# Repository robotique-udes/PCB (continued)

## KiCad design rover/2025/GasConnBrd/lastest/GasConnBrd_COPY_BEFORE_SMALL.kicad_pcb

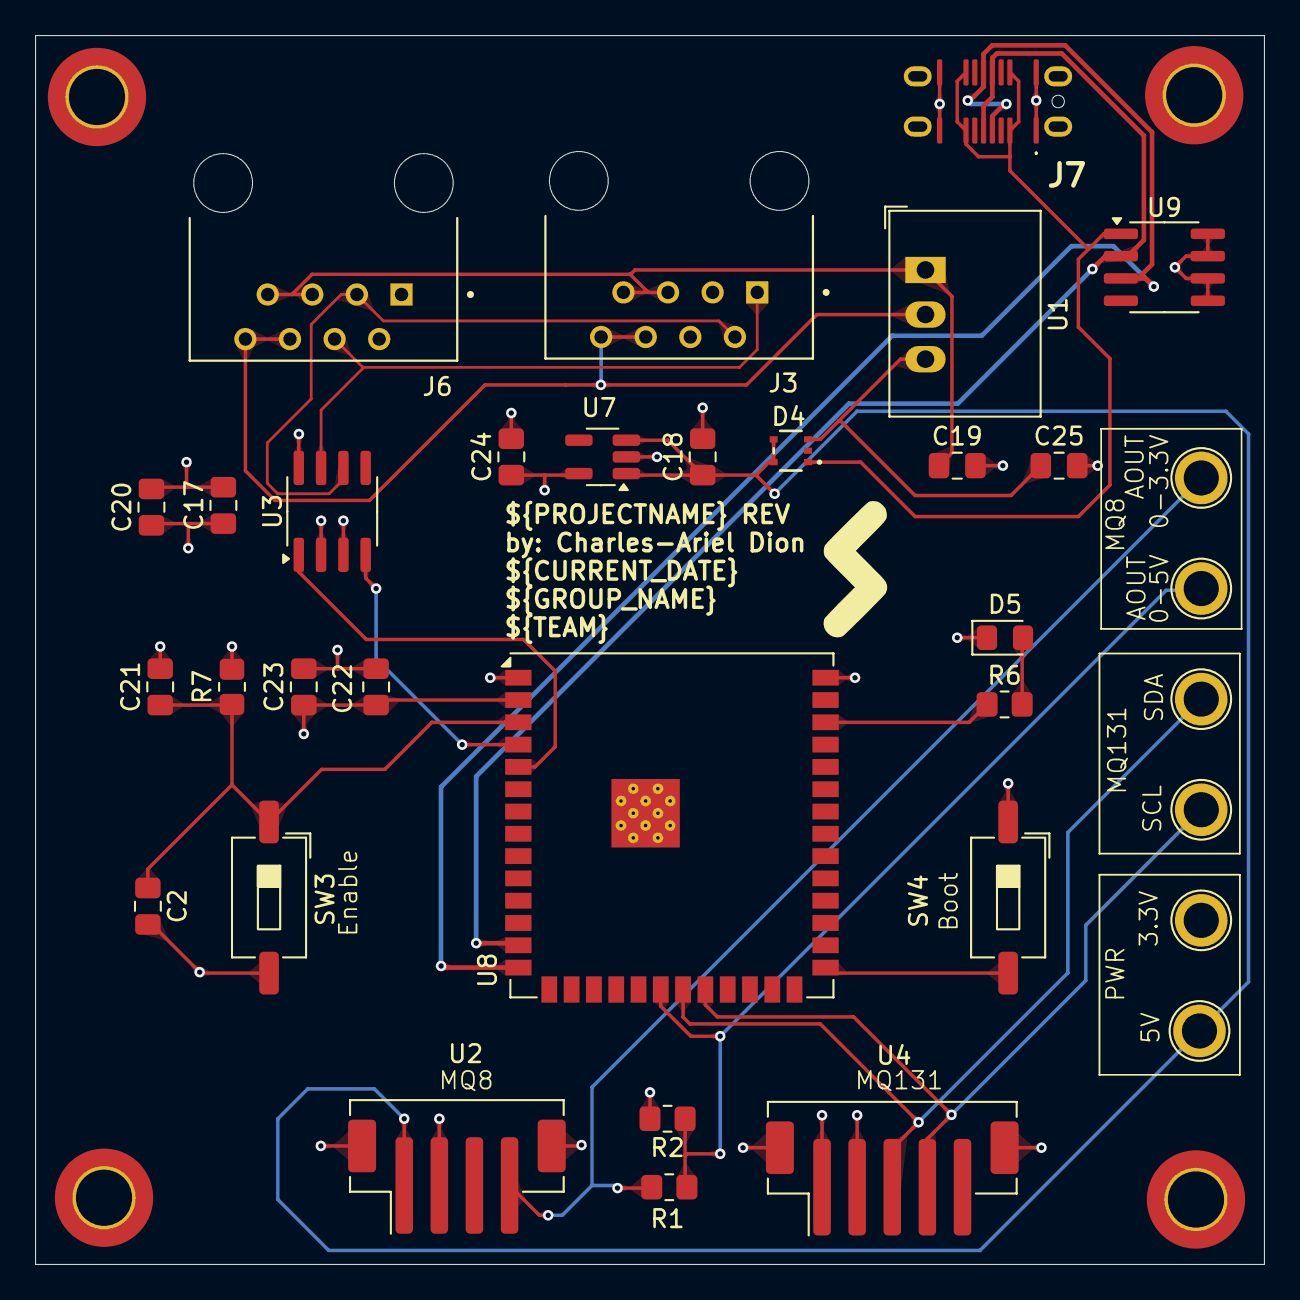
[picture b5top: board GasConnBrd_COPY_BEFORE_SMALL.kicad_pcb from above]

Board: 4 copper layers, 70.0 x 70.0 mm, 38 parts (0 on the bottom side), 20 nets.

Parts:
C2, C20, C23: 100nF; C_0805_2012Metric_Pad1.18x1.45mm_HandSolder
C17, C18, C19, C22, C24, C25: 10uF; C_0805_2012Metric_Pad1.18x1.45mm_HandSolder
C21: 1uF; C_0805_2012Metric_Pad1.18x1.45mm_HandSolder
D4: CVJ10F30; Diode_schottky-CVJ10F30
D5: B; LED_0805_2012Metric_Pad1.15x1.40mm_HandSolder
H9, H10, H11, H12: MountingHole_Pad; MountingHole
J3, J6: Eth-Horiz; Ethernet_Horizontal
J7: USB_C_USB4145-GCT; USB4145_GCT
R1, R7: 10k; R_0805_2012Metric_Pad1.20x1.40mm_HandSolder
R2: 20k; R_0805_2012Metric_Pad1.20x1.40mm_HandSolder
R6: 1k; R_0805_2012Metric_Pad1.20x1.40mm_HandSolder
SW3, SW4: TS09-63-25-WT-160-SMT-TR; SW_DIP_SPSTx01_Slide_6.7x4.1mm_W8.61mm_P2.54mm_LowProfile
TP1, TP2, TP3, TP4, TP6, TP7: TestPoint; TestPoint_Plated_Hole_D2.0mm
U1: R-78E5.0-0.5; Converter_DCDC_RECOM_R-78E-0.5_THT
U2: MQ-8; JST_PH_B4B-PH-SM4-TB_1x04-1MP_P2.00mm_Vertical
U3: SN65HVD232; SOIC-8_3.9x4.9mm_P1.27mm
U4: MQ-131; JST_PH_B5B-PH-SM4-TB_1x05-1MP_P2.00mm_Vertical
U7: LDO-TLV74033PDBVR; SOT-23-5_HandSoldering
U8: ESP32-S3-WROVER; ESP32-S3-WROOM-1U
U9: TVS; SOIC-8_3.9x4.9mm_P1.27mm

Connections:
+3.3V: C17.1, C20.1, C22.1, C23.2, C24.1, R7.1, TP6.1, U3.3 (VCC), U4.1 (3.3V), U7.5 (OUTPUT), U8.2 (3V3)
+5V: C18.1, D4.4, D4.5, TP7.1, U2.1 (5V), U7.1 (INPUT), U7.3 (EN)
+5V_ETH: C25.1, D4.3, U1.3 (OUT)
+5V_USB: D4.1, J7.A4 (VBUS), J7.A9 (VBUS), J7.B4 (VBUS), J7.B9 (VBUS), U9.1
+24V: C19.1, J3.5, J3.7, J6.5, J6.7, U1.1 (IN)
/Sensors/MQ8_AOUT_5V: R1.1 (+), TP1.1, U2.4 (A0)
CAN_N: J3.2 (CANL), J6.3, U3.6 (CANL)
CAN_P: J3.1 (CANH), J6.4, U3.7 (CANH)
EN_ESP: C2.1, C21.1, R7.2, SW3.1, U8.3 (EN)
GND: C2.2, C17.2, C18.2, C19.2, C20.2, C21.2, C22.2, C23.1, C24.2, C25.2, D5.1 (K), H9.1, H10.1, H11.1, H12.1, J3.6, J3.8, J6.6, J6.8, J7.A1 (GND), J7.A12 (GND), J7.B1 (GND), J7.B12 (GND), R2.2 (-), SW3.2, SW4.1, U1.2 (GND), U2.2 (GND), U3.2 (GND), U3.8 (S), U4.2 (GND), U7.2 (GND), U8.1 (GND), U8.40 (GND), U8.41 (GND), U9.5, U9.6, U9.7, U9.8
GPIO_0: SW4.2, U8.27 (IO0-BOOT)
LED_BUILDIN: R6.1, U8.38 (IO2)
MQ8_AOUT: R1.2 (-), R2.1 (+), TP4.1, U8.20 (IO12)
MQ131_SCL: TP3.1, U4.4 (SCL), U8.22 (IO14)
MQ131_SDA: TP2.1, U4.3 (SDA), U8.21 (IO13)
unnamed: D5.2 (A), R6.2
RXC: U3.1 (TXD), U8.5 (IO5)
TXC: U3.4 (RXD), U8.4 (IO4)
USB_N: J7.A7 (D-), J7.B7 (D-), U8.13 (IO19-USB_N), U9.2
USB_P: J7.A6 (D+), J7.B6 (D+), U8.14 (IO20-USB-P), U9.3

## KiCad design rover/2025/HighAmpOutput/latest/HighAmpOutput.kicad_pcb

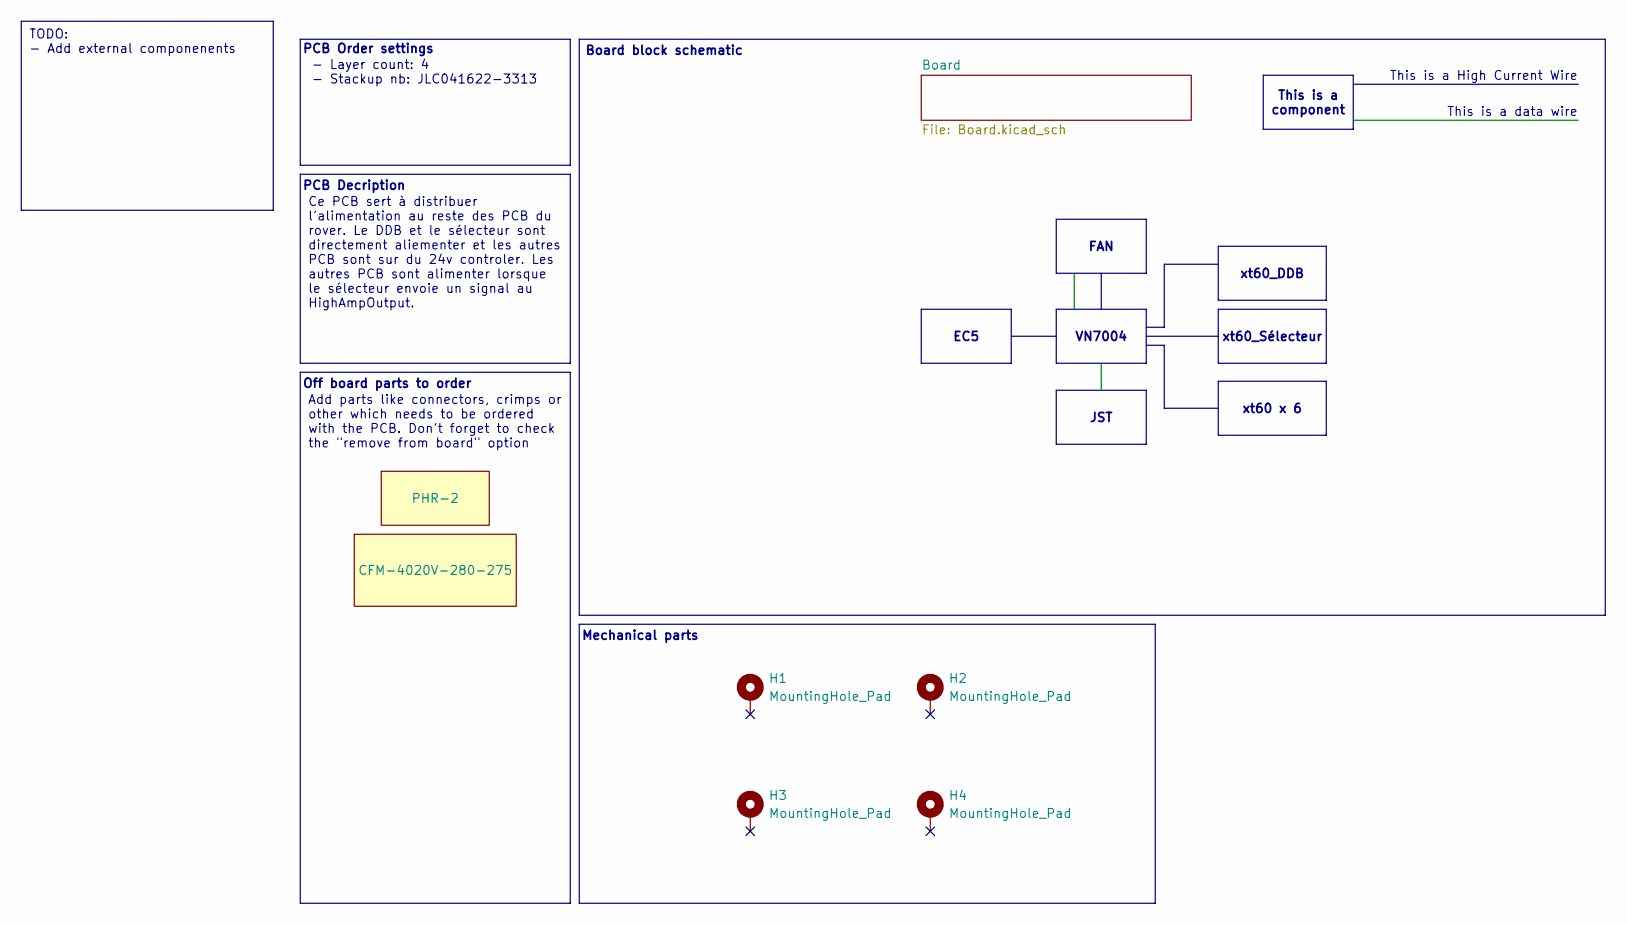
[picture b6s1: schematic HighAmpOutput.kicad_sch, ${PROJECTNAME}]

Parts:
G1: PHR-2
G2: CFM-4020V-280-275
H1, H2, H3, H4: MountingHole_Pad; MountingHole_3.2mm_M3_DIN965_Pad_TopBottom

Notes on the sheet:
This is a component
xt60_DDB
xt60_Sélecteur
Ce PCB sert à distribuer l'alimentation au reste des PCB du rover. Le DDB et le sélecteur sont directement aliementer et les autres PCB sont sur du 24v controler. Les autres PCB sont alimenter lorsque le sélecteur envoie un signal au HighAmpOutput.
EC5
TODO: - Add external componenents
JST
Add parts like connectors, crimps or other which needs to be ordered with the PCB. Don't forget to check the "remove from board" option
VN7004
xt60 x 6
FAN
Off board parts to order
Mechanical parts
This is a data wire
- Layer count: 4 - Stackup nb: JLC041622-3313
PCB Decription
Board block schematic
This is a High Current Wire
PCB Order settings

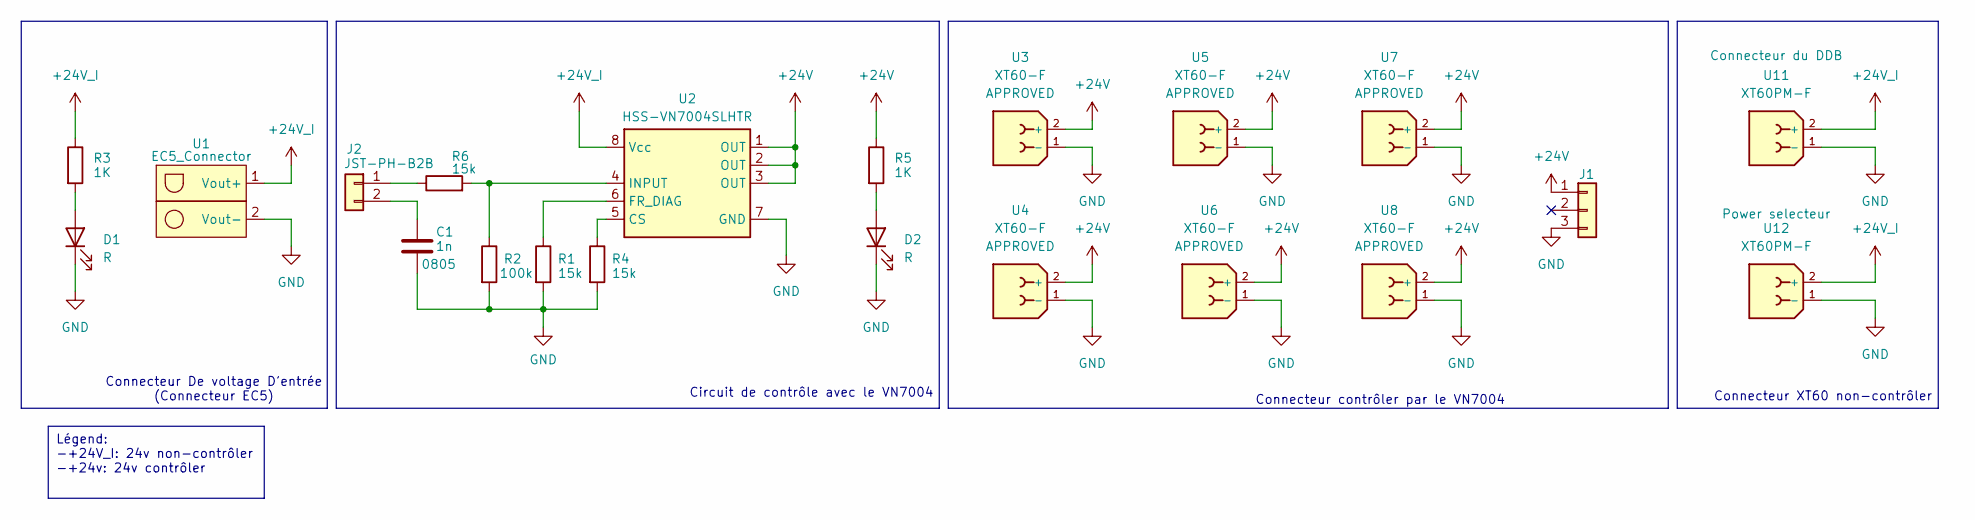
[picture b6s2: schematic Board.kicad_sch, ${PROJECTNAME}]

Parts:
C1: 1n; C_0805_2012Metric_Pad1.18x1.45mm_HandSolder
D1, D2: R; LED_0805_2012Metric_Pad1.15x1.40mm_HandSolder
J1: Conn_01x03; JST_PH_B3B-PH-K_1x03_P2.00mm_Vertical
J2: JST-PH-B2B; JST_PH_B2B-PH-K_1x02_P2.00mm_Vertical
R1, R4, R6: 15k; R_0805_2012Metric_Pad1.20x1.40mm_HandSolder
R2: 100k; R_0805_2012Metric_Pad1.20x1.40mm_HandSolder
R3, R5: 1K; R_0805_2012Metric_Pad1.20x1.40mm_HandSolder
U1: EC5_Connector; EC5
U2: HSS-VN7004SLHTR; OCTAPACK_VN7004_STM-M
U3, U4, U5, U6, U7, U8: XT60-F; AMASS_XT60-F_1x02_P7.20mm_Vertical
U11, U12: XT60PM-F; AMASS_XT60PW-F_1x02_P7.20mm_Horizontal

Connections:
+24V: J1.1, R5.1, U2.1 (OUT), U2.2 (OUT), U2.3 (OUT), U3.2 (+), U4.2 (+), U5.2 (+), U6.2 (+), U7.2 (+), U8.2 (+)
+24V_I: R3.1, U1.1 (Vout+), U2.8 (Vcc), U11.2 (+), U12.2 (+)
GND: C1.2, D1.1 (K), D2.1 (K), J1.3, R1.2, R2.2, R4.2, U1.2 (Vout-), U2.7 (GND), U3.1 (-), U4.1 (-), U5.1 (-), U6.1 (-), U7.1 (-), U8.1 (-), U11.1 (-), U12.1 (-)
unnamed: D1.2 (A), R3.2
unnamed: D2.2 (A), R5.2
unnamed: J2.1, R6.1
unnamed: C1.1, J2.2
unnamed: R4.1, U2.5 (CS)
unnamed: R1.1, U2.6 (FR_DIAG)
unnamed: R2.1, R6.2, U2.4 (INPUT)

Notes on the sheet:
Légend: -+24V_I: 24v non-contrôler -+24v: 24v contrôler
Connecteur XT60 non-contrôler
Connecteur contrôler par le VN7004
Connecteur De voltage D'entrée (Connecteur EC5)
Circuit de contrôle avec le VN7004

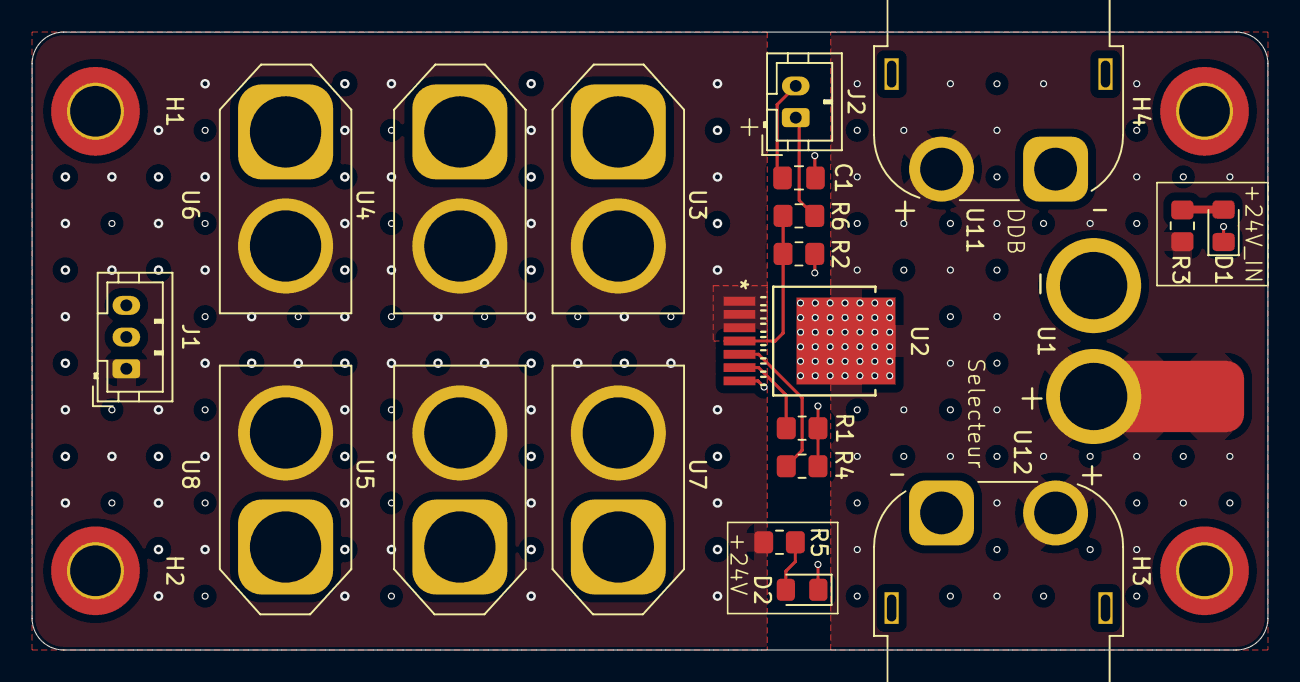
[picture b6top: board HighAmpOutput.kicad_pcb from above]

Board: 4 copper layers, 78.0 x 39.0 mm, 25 parts (0 on the bottom side), 10 nets.
